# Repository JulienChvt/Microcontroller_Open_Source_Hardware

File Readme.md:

# Connected Gas Sensor

Project done for the **MICROCONTROLLERS AND OPEN-SOURCE HARDWARE** course of **INSA Toulouse**.

**Authors :** Jean-Baptiste Laffosse - Julien Chouvet

# General

The aim of this project is to build a **connected gas sensor**.

To be more specific, we use **RN2483** chip, connected to an       **Arduino Uno**, to send on the **LoRa Network** the values returned by the **MQ-9 gas sensor**. Thanks to **The Things Network** and **Node-RED** we create a **dashboard** as a **user interface**. In this dashboard, the user can **monitor the value of the gas sensor** and **calibrate** it.

We also add a **gas alert function** which is triggered when the value return by the MQ-9 goes over a threshold value. As we cannot attach an interrupt on a analog input, to do this, we used a **Schmitt trigger** connected to a numerical pin of the Arduino Uno. Thus, when an alert is detected (rising or falling edge, mode **CHANGE**), the interruption triggered a function. The user is informed of this alert by a **buzzer** and by a **message displayed on the dashboard**.

Finally, we develop a shield that we can plug on the **Arduino Uno** microcontroller. So we use **KiCAD** to sketch all the circuits of the shield.

## Hardware Components

**- Arduino Uno** : https://store.arduino.cc/usa/arduino-uno-rev3

**- MQ-9 Gas Sensor** : http://www.mouser.com/catalog/specsheets/Seeed_101020045.pdf

**- Microchip RN2483** : http://ww1.microchip.com/downloads/en/DeviceDoc/50002346C.pdf

**- Operational Amplifier LM741** : http://www.ti.com/lit/ds/symlink/lm741.pdf 

## Arduino code

For this project we used an **Arduino Uno board**.

We developed the code on the **Arduino IDE** : https://www.arduino.cc/en/Main/Software

The source code of the project is available on the *GasSensor_TTN_LoRa directory*.

You can find more information on this code on our report.

## Schmitt trigger

We use a Schmitt trigger to detect when the value of the gas sensor goes over a threshold value.

The design and the LTSpice simulation of this electronic circuit are available on the *Schmitt_Trigger directory*.

You can find more information on the Schmitt trigger on our report.

## The Things Network

The Things Network (TTN) is a worldwide community LoRa network provided an end-to-end stack for IoT. 
To configure TTN follow these steps :

 1. Go to https://www.thethingsnetwork.org/ and create an account
 2. Create an **application** : https://www.thethingsnetwork.org/docs/applications/add.html
 3. Add a **device** in your application : https://www.thethingsnetwork.org/docs/devices/registration.html
 **Note :** we use **ABP** activation method

You can find more information on how we used TTN to send/receive messages to/from the Arduino, on the Arduino code and also on the report.
You can also find the **Decoder** and **Validator function** on the *TTN directory*.

## Node-RED

Node-RED is a flow-based development tool for visual programming developed originally by IBM for wiring together hardware devices, APIs and online services as part of the Internet of Things. (source : https://en.wikipedia.org/wiki/Node-RED#cite_note-2)

We used it to create a dashboard, in which the user can see the value of the gas sensor and can also ask to calibrate the sensor.

To install Node-RED for TTN follow these steps :

 1. Follow this tutorial to install Node.js and NodeRED : https://nodered.org/docs/getting-started/installation

 2. To send/receive messages to/from devices through TTN, you need to install the TTN node for NodeRed :

        cd  $HOME/.node-red
        npm install node-red-contrib-ttn

 3. To create a dashboard, you need to install a specific module :

		cd  $HOME/.node-red
        npm install node-red-dashboard
    
To run Node-RED, open a prompt and type *node-red*. Then open a browser and type the following URL : *http://127.0.0.1:1880/*

You can find the Node-RED flow made for this project in the *Node_RED directory*.
Have a look at our report for more information.    

## KiCAD

KiCad is an **open-source software tool** for the creation of **electronic schematic diagrams** and **PCB artwork**. The main avantage with KiCAD is that the software offers a **singular interface** for all the steps needed during the **development of the shield**. This is why we choose KiCAD to develop our shield. 

You can find all the documentation needed here : 
http://docs.kicad-pcb.org/stable/en/getting_started_in_kicad.html

To develop the shield or open our files, you need to follow these steps :

1. First, you need to download KiCAD at the following address and choose your operating system. **KiCAD** will allow you to open the project file **.pro** of the shield. 
http://www.kicad-pcb.org/download/

2. You can start sketching your circuit thanks to **Eeschema**. If your component does not exist you can create it or import it from an external library. With **Eeschema**, you can open all the **.sch, .lib, .net files**, and like this see our circuit contained in the **.sch file**.

3. **Annotate**, and perform the **rule check**. Make sure you don't have any errors. Then you can **associate each component with their footprint**.

4. Generate the **Netlist** of your schematic, in fact you will generate a **.net file**.

5. You can now create your PCB. For this open **PCBnew** and read the **Netlist**. Perform the **rule check** and make sure you don't have any errors. PCBnew allows you to open all the ** *.kicad_pcb and *.kicad_mod files**, and our PCB is contained in the **.kicad_pcb file**.

6. Export your **Gerber file** from PCBnew. If you want, you can inspect your file from **GerbView**. All the gerber files generated can have either the default **.gbr** extension, or the **.g** extension (one for each layer) :
http://docs.kicad-pcb.org/stable/en/getting_started_in_kicad.html#generate-gerber-files

On the *KiCAD directory* you can find two projects :

 1. Design of an Arduino Board with the Schmitt Trigger and a socket for the *MQ-9* gas sensor. This design corresponds to the project describe so far.
 2.  Design of an Arduino Uno board with the gas sensor and a transimpedance montage.

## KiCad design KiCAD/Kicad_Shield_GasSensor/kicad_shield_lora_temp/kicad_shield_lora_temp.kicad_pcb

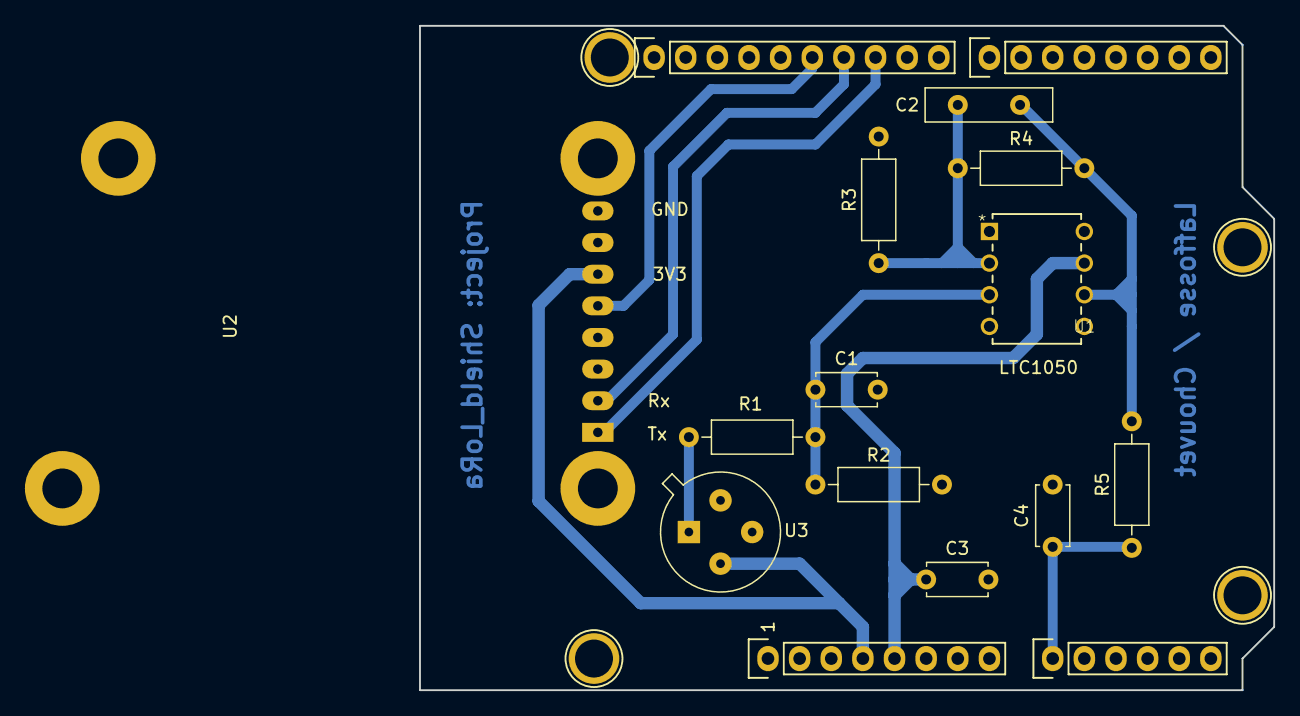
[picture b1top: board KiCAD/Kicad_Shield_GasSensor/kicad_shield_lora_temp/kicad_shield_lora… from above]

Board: 2 copper layers, 68.6 x 53.3 mm, 20 parts (0 on the bottom side), 13 nets.

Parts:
3V3: Analog; Socket_Strip_Arduino_1x06
C1, C3, C4: 100n; C_Disc_D4.7mm_W2.5mm_P5.00mm
C2: 1µ; C_Disc_D10.0mm_W2.5mm_P5.00mm
GND: Digital; Socket_Strip_Arduino_1x08
P5, P6, P7, P8: CONN_01X01; Arduino_1pin
R1: 10k; R_Axial_DIN0207_L6.3mm_D2.5mm_P10.16mm_Horizontal
R2, R4: 100k; R_Axial_DIN0207_L6.3mm_D2.5mm_P10.16mm_Horizontal
R3, R5: 1k; R_Axial_DIN0207_L6.3mm_D2.5mm_P10.16mm_Horizontal
Rx: Power; Socket_Strip_Arduino_1x08
Tx: Digital; Socket_Strip_Arduino_1x10
U1: LTC1050
U2: shield_RN2483
U3: GasSensor; TO-5-4_cap_gaz

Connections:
+3V3: Rx.4, U2.6, U3.2
+5V: C3.1, Rx.5, U1.7
/10(**/SS): Tx.8, U2.1
/11(**/MOSI): Tx.7, U2.2
/12(MISO): Tx.6, U2.5
/A0: 3V3.1, C4.1, R5.1
/A4(SDA): 3V3.5, Tx.2
/A5(SCL): 3V3.6, Tx.1
GND: C1.2, C3.2, C4.2, R2.2, R3.2, Rx.6, Rx.7, Tx.4, U1.4, U2.8
unnamed: C1.1, R1.1, R2.1, U1.3
unnamed: C2.1, R3.1, R4.1, U1.2
unnamed: C2.2, R4.2, R5.2, U1.6
unnamed: R1.2, U3.1

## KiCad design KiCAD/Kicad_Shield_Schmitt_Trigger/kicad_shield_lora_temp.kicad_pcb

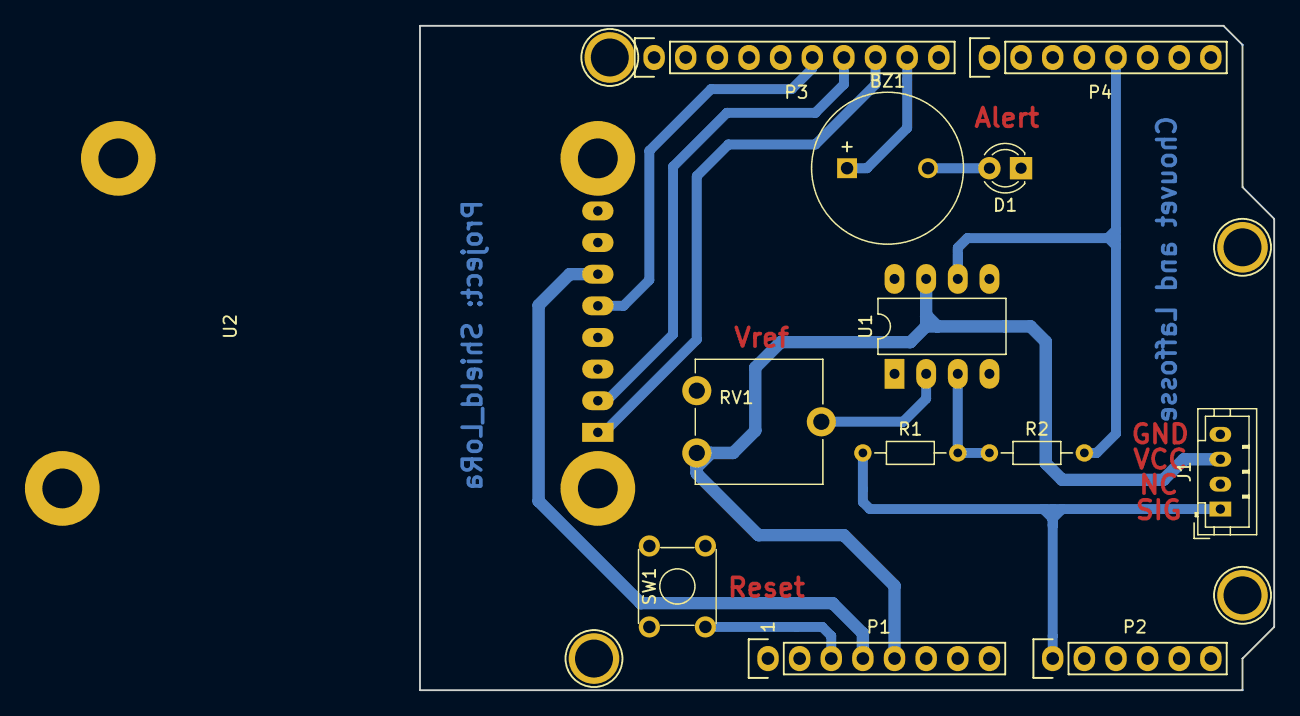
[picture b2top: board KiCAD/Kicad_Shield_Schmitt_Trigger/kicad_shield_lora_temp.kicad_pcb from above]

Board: 2 copper layers, 68.6 x 53.3 mm, 17 parts (0 on the bottom side), 15 nets.

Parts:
BZ1: Buzzer; MagneticBuzzer_ProSignal_ABT-410-RC
D1: LED; LED_D3.0mm
J1: Conn_01x04_Male_Sensor; JST_PH_B4B-PH-K_1x04_P2.00mm_Vertical
P1: Power; Socket_Strip_Arduino_1x08
P2: Analog; Socket_Strip_Arduino_1x06
P3: Digital; Socket_Strip_Arduino_1x10
P4: Digital; Socket_Strip_Arduino_1x08
P5, P6, P7, P8: CONN_01X01; Arduino_1pin
R1: 4.7k; R_Axial_DIN0204_L3.6mm_D1.6mm_P7.62mm_Horizontal
R2: 100k; R_Axial_DIN0204_L3.6mm_D1.6mm_P7.62mm_Horizontal
RV1: 10k; Potentiometer_ACP_CA9-V10_Vertical
SW1: SW_Push_Dual; SW_TH_Tactile_Omron_B3F-10xx
U1: LM741; DIP-8_W7.62mm_LongPads
U2: shield_RN2483

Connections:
+3V3: P1.4, U2.6
+5V: J1.3, P1.5, RV1.1, U1.7
/3(**): P4.5, R2.2, U1.6
/9(**): BZ1.1, P3.9
/10(**/SS): P3.8, U2.1
/11(**/MOSI): P3.7, U2.2
/12(MISO): P3.6, U2.5
/A0: J1.1, P2.1, R1.1
/A4(SDA): P2.5, P3.2
/A5(SCL): P2.6, P3.1
/Reset: P1.3, SW1.3
GND: D1.1, J1.4, P1.6, P1.7, P3.4, RV1.3, SW1.4, U1.4, U2.8
unnamed: BZ1.2, D1.2
unnamed: R1.2, R2.1, U1.3
unnamed: RV1.2, U1.2

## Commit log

2018-11-28 add files of the project
2018-11-30 Unzip files on KiCAS directory
2018-11-30 Add model file of AOPLM741 for the Spice simulation of the Schmitt Trigger
2018-11-30 add report
